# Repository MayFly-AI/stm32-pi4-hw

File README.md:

This repository contains 

- KiCad files for Raspberry Pi HAT Pose sensor
- KiCad files for STM32 Pose sensor
- STL files for camera enclosure
- STL files for enclosure for STM32 Pose sensor

We have used JLCPCB for producing the PCBs and the enclosures.

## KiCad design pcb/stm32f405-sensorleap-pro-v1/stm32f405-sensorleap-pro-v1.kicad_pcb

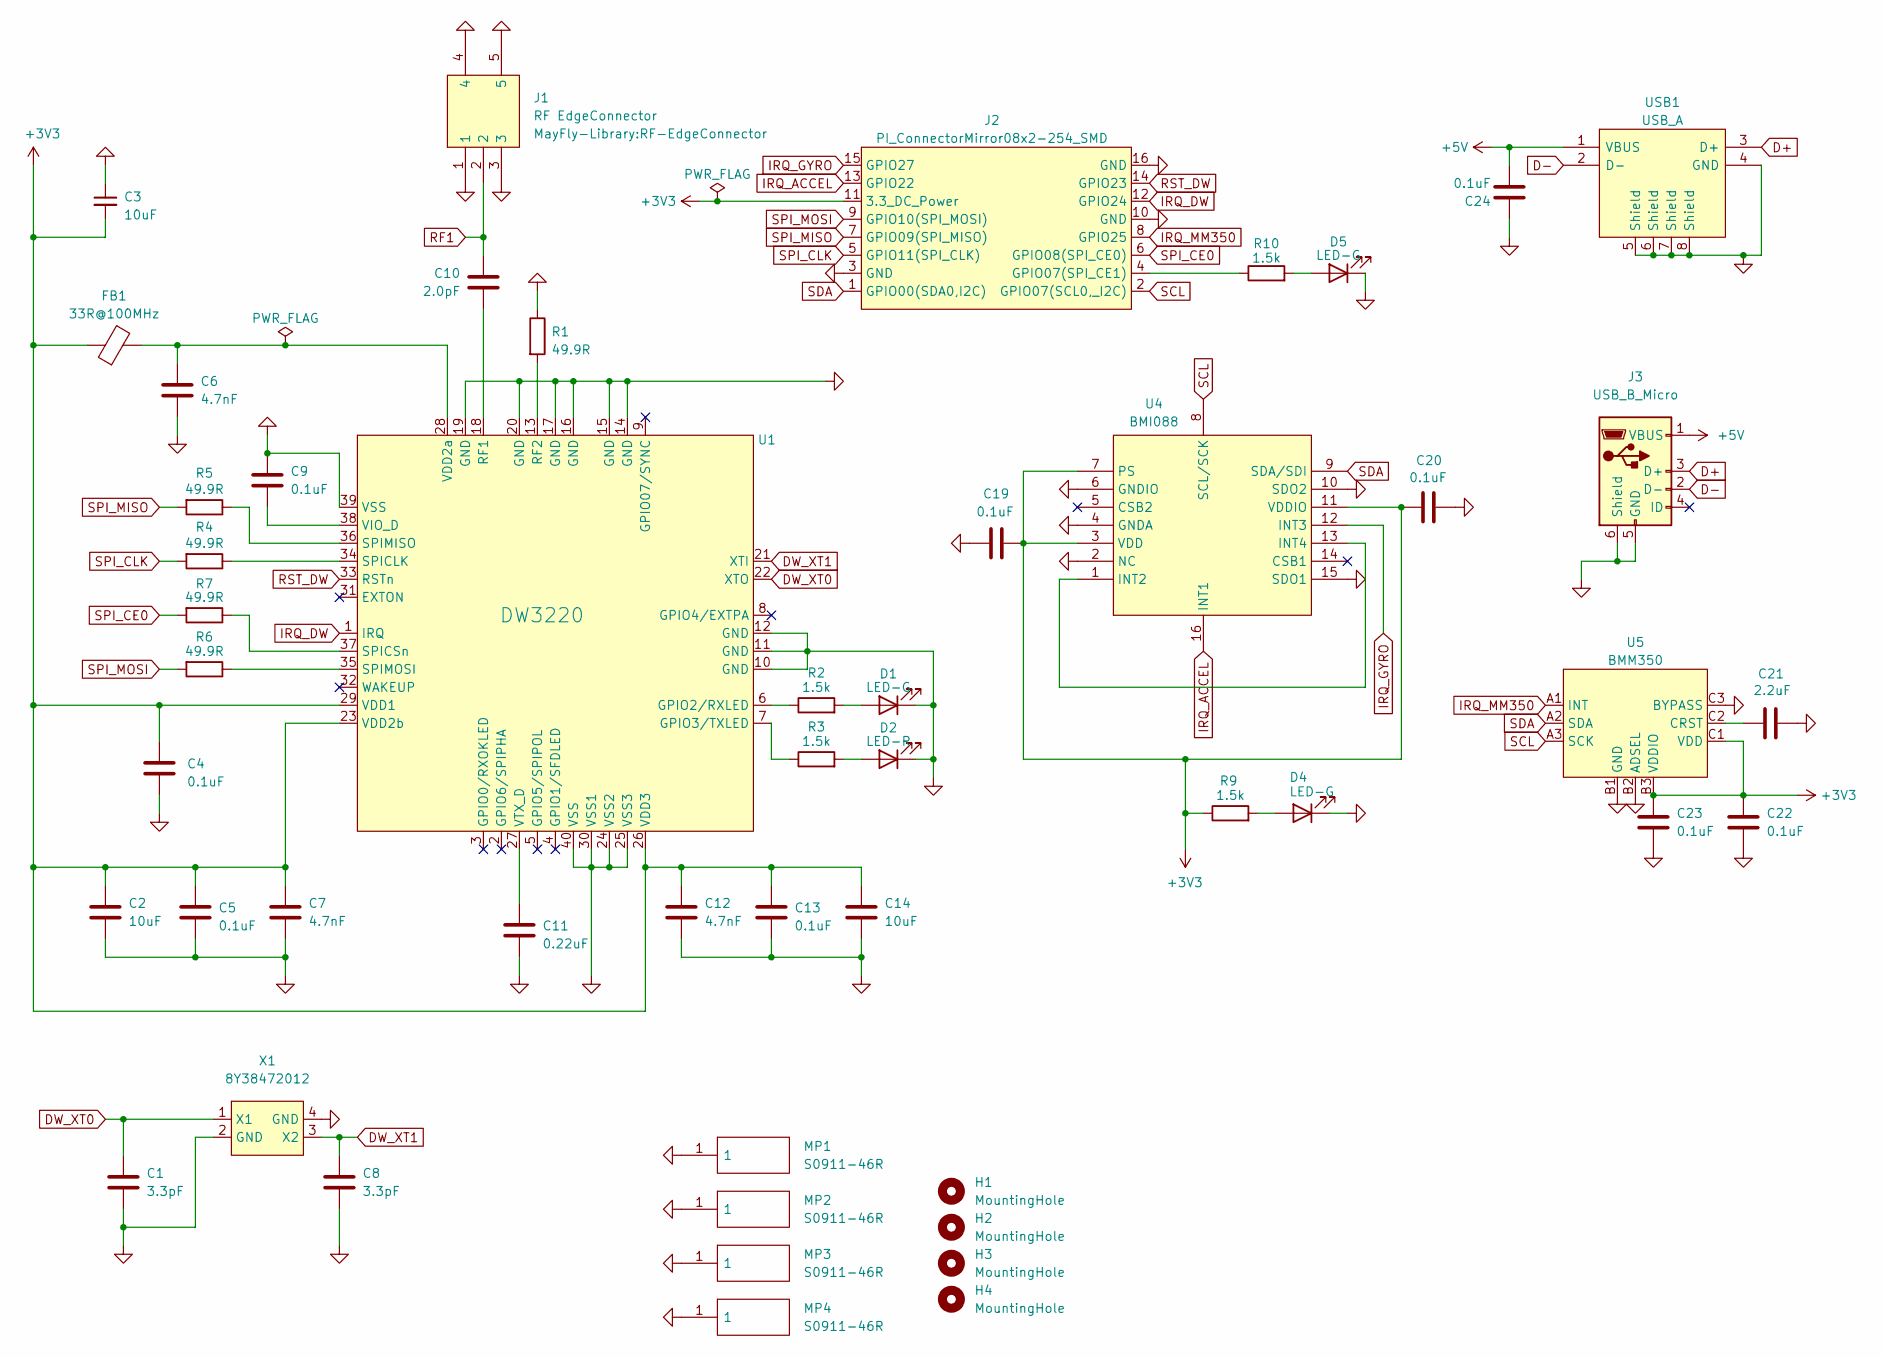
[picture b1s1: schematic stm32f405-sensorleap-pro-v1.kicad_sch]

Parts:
C1, C8: 3.3pF; C_0402_1005Metric; Mouser 81-GJM1555C1H3R3WB1D
C2, C14: 10uF; C_0402_1005Metric; Mouser 81-GRM155R61A106ME1D
C3: 10uF; C_0603_1608Metric; Mouser 81-GRM188R60J106ME47
C4, C5, C9, C13, C19, C20, C22, C23, C24: 0.1uF; C_0402_1005Metric; Mouser 810-C1005X7R1H104KBE
C6, C7, C12: 4.7nF; C_0402_1005Metric; Mouser 81-GCM155R71H472K37D
C10: 2.0pF; C_0402_1005Metric; Mouser 81-GJM1555C1H2R0WB1D
C11: 0.22uF; C_0402_1005Metric; Mouser 81-GRM155R71A224KE1D
C21: 2.2uF; C_0805_2012Metric; Mouser 81-GCM21BR71A225KA7L
D1, D4, D5: LED-G; LED_0603_1608Metric; LCSC C264453
D2: LED-R; LED_0603_1608Metric; LCSC C181863
FB1: 33R@100MHz; L_0402_1005Metric; Mouser 81-BLM15PX330SZ1D
H1, H2, H3, H4: MountingHole; MountingHole_2.5mm
J1: RF EdgeConnector; RF-EdgeConnector
J2: PI_ConnectorMirror08x2-254_SMD; PI_Connector08x2-254_SMD; LCSC C5160823
J3: USB_B_Micro; USB_Micro-AB_Molex_47590-0001; LCSC C136001
MP1, MP2, MP3, MP4: S0911-46R; S091146R; Mouser Part Number 855-S0911-46R
R1, R4, R5, R6, R7: 49.9R; R_0402_1005Metric; Mouser 667-ERJ-2RKF49R9X
R2, R3, R9, R10: 1.5k; R_0402_1005Metric; Mouser 667-ERJ-2RKF1501X
U1: DW3220; QFN-40_5x5_Pitch0.4mm; Mouser 772-DW3220TR13
U4: BMI088; Mouser :262-BMI088
U5: BMM350; LCSC C7496950
USB1: USB_A; 629104190121; Mouser Part Number 710-629104190121
X1: 8Y38472012; LCSC C2450882

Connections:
+3V3: C2.1, C3.2, C4.1, C5.1, C7.1, C12.1, C13.1, C14.1, C19.2, C20.1, C22.1, C23.1, FB1.1, J2.11 (3.3_DC_Power), R9.1, U1.23 (VDD2b), U1.26 (VDD3), U1.29 (VDD1), U4.3 (VDD), U4.7 (PS), U4.11 (VDDIO), U5.B3 (VDDIO), U5.C1 (VDD)
+5V: C24.2, J3.1 (VBUS), USB1.1 (VBUS)
D+: J3.3 (D+), USB1.3 (D+)
D-: J3.2 (D-), USB1.2 (D-)
DW_XT0: C1.1, U1.22 (XTO), X1.1 (X1)
DW_XT1: C8.1, U1.21 (XTI), X1.3 (X2)
GND: C1.2, C2.2, C3.1, C4.2, C5.2, C6.2, C7.2, C8.2, C9.1, C11.2, C12.2, C13.2, C14.2, C19.1, C20.2, C21.2, C22.2, C23.2, C24.1, D1.1 (K), D2.1 (K), D4.1 (K), D5.1 (K), J1.1, J1.3, J1.4, J1.5, J2.3 (GND), J2.10 (GND), J2.16 (GND), J3.5 (GND), J3.6 (Shield), MP1.1, MP2.1, MP3.1, MP4.1, R1.1, U1.10 (GND), U1.11 (GND), U1.12 (GND), U1.14 (GND), U1.15 (GND), U1.16 (GND), U1.17 (GND), U1.19 (GND), U1.20 (GND), U1.24 (VSS2), U1.25 (VSS3), U1.30 (VSS1), U1.39 (VSS), U1.40 (VSS), U4.2 (NC), U4.4 (GNDA), U4.6 (GNDIO), U4.10 (SDO2), U4.15 (SDO1), U5.B1 (GND), U5.B2 (ADSEL), U5.C3 (BYPASS), USB1.4 (GND), USB1.5 (Shield), USB1.6 (Shield), USB1.7 (Shield), USB1.8 (Shield), X1.2 (GND), X1.4 (GND)
IRQ_ACCEL: J2.13 (GPIO22), U4.16 (INT1)
IRQ_DW: J2.12 (GPIO24), U1.1 (IRQ)
IRQ_GYRO: J2.15 (GPIO27), U4.12 (INT3)
IRQ_MM350: J2.8 (GPIO25), U5.A1 (INT)
unnamed: D1.2 (A), R2.2
unnamed: D2.2 (A), R3.2
unnamed: D4.2 (A), R9.2
unnamed: D5.2 (A), R10.2
unnamed: J2.4 (GPIO07(SPI_CE1)), R10.1
unnamed: R2.1, U1.6 (GPIO2/RXLED)
unnamed: R3.1, U1.7 (GPIO3/TXLED)
unnamed: C10.2, U1.18 (RF1)
unnamed: R1.2, U1.13 (RF2)
unnamed: R4.1, U1.34 (SPICLK)
unnamed: R7.1, U1.37 (SPICSn)
unnamed: R5.1, U1.36 (SPIMISO)
unnamed: R6.1, U1.35 (SPIMOSI)
unnamed: C6.1, FB1.2, U1.28 (VDD2a)
unnamed: C9.2, U1.38 (VIO_D)
unnamed: C11.1, U1.27 (VTX_D)
unnamed: U4.1 (INT2), U4.13 (INT4)
unnamed: C21.1, U5.C2 (CRST)
RF1: C10.1, J1.2
RST_DW: J2.14 (GPIO23), U1.33 (RSTn)
SCL: J2.2 (GPIO07(SCL0,_I2C)), U4.8 (SCL/SCK), U5.A3 (SCK)
SDA: J2.1 (GPIO00(SDA0,I2C)), U4.9 (SDA/SDI), U5.A2 (SDA)
SPI_CE0: J2.6 (GPIO08(SPI_CE0)), R7.2
SPI_CLK: J2.5 (GPIO11(SPI_CLK)), R4.2
SPI_MISO: J2.7 (GPIO09(SPI_MISO)), R5.2
SPI_MOSI: J2.9 (GPIO10(SPI_MOSI)), R6.2

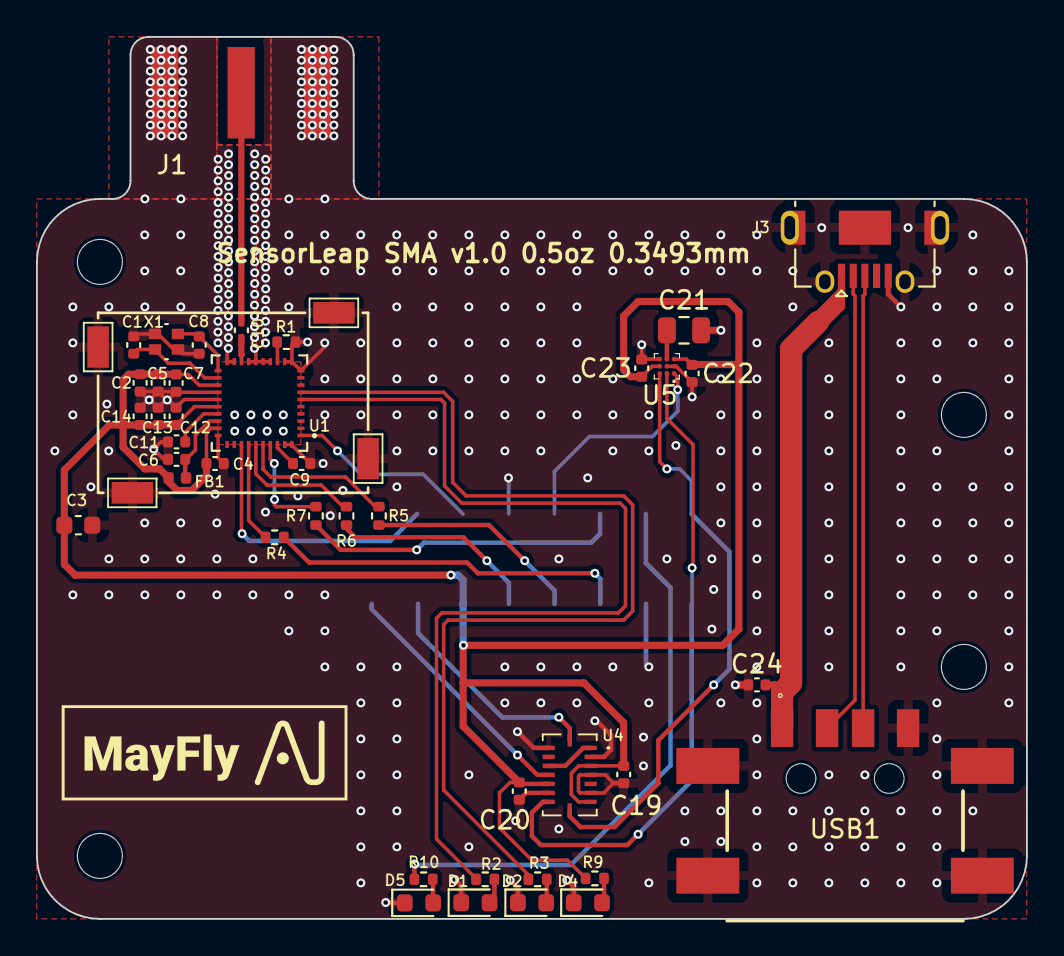
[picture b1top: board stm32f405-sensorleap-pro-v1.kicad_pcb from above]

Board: 4 copper layers, 55.0 x 49.0 mm, 50 parts (1 on the bottom side), 37 nets.

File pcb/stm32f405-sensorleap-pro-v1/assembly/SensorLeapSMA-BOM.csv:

Comment,Designator,Footprint,LCSC
3.3pF,"C1,C8",Capacitor_SMD:C_0402_1005Metric,C88892
2.0pF,C10,Capacitor_SMD:C_0402_1005Metric,C88885
0.22uF,C11,Capacitor_SMD:C_0402_1005Metric,C180472
10uF,"C2,C14",Capacitor_SMD:C_0402_1005Metric,C408132
2.2uF,C21,Capacitor_SMD:C_0805_2012Metric,C126587
10uF,C3,Capacitor_SMD:C_0603_1608Metric,C77041
0.1uF,"C4,C5,C9,C13,C19,C20,C22,C23,C24",Capacitor_SMD:C_0402_1005Metric,C432917
4.7nF,"C6,C7,C12",Capacitor_SMD:C_0402_1005Metric,C85860
LED-G,"D1,D4,D5",LED_SMD:LED_0603_1608Metric,C264453
LED-R,D2,LED_SMD:LED_0603_1608Metric,C181863
33R@100MHz,FB1,Inductor_SMD:L_0402_1005Metric,C2661673
USB_B_Micro,J3,MayFly-Library:USB_Micro-AB_Molex_47590-0001,C136001
49.9R,"R1,R4,R5,R6,R7",Resistor_SMD:R_0402_1005Metric,C441726
1.5k,"R2,R3,R9,R10",Resistor_SMD:R_0402_1005Metric,C413084
DW3220,U1,MayFly-Library:QFN-40_5x5_Pitch0.4mm,C5441013
BMI088,U4,SamacSys_Parts:BMI088,C194919
BMM350,U5,MayFly-Library:BMM350,C7496950
USB_A,USB1,SamacSys_Parts:629104190121,C530629
8Y38472012,X1,MayFly-Library:8Y38472012,C2450882

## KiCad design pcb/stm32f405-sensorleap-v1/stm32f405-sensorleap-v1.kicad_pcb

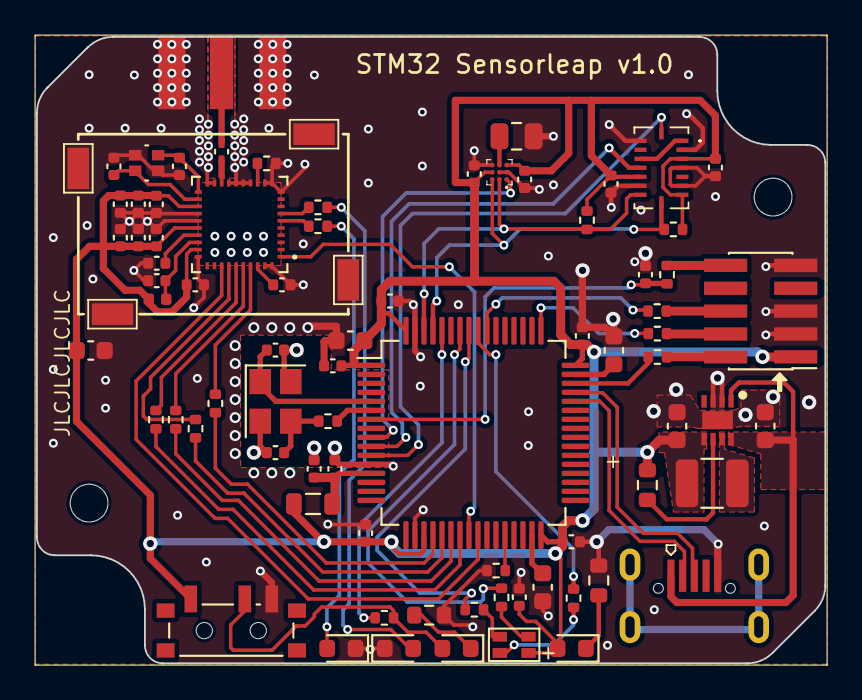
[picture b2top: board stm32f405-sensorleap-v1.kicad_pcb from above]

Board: 4 copper layers, 43.8 x 34.8 mm, 82 parts (0 on the bottom side), 61 nets.

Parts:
C1, C301: 10uF; C_0603_1608Metric
C2, C14: 10uF; C_0402_1005Metric
C3, C9: 3.3pF; C_0402_1005Metric
C4, C6, C7, C13, C15, C16, C18, C19: 0.1uF; C_0402_1005Metric
C5, C8, C12: 4.7nF; C_0402_1005Metric
C10: 2.0pF; C_0402_1005Metric
C11: 0.22uF; C_0402_1005Metric
C20: 2.2uF; C_0805_2012Metric
C200: 4u7; C_0603_1608Metric
C201, C202, C203, C204, C205, C212, C400: 100n; C_0402_1005Metric
C206: 1u; C_0402_1005Metric
C207: 10n; C_0402_1005Metric
C208, C209: 2u2; C_0603_1608Metric
C210, C211: 12p; C_0402_1005Metric
C302: 22uF; C_0603_1608Metric
D1, D102: LED-G; LED_0603_1608Metric
D2, D200: LED-R; LED_0603_1608Metric
D201: 19-237/R6GHBHC-A01/2T; 19-237-R6GHBHC-A01-2T
FB1: 33R@100MHz; L_0402_1005Metric
FB200: 600 @ 600 MHz; L_0805_2012Metric
H1, H2: MountingHole; MountingHole_2.1mm
J1: RF EdgeConnector; CON-SMA-EDGE-SRP
J401: SWD; PinHeader_2x05_P1.27mm_Vertical_SMD
J402: USB_B_Micro; 5P Female Micro-B C40943
L1: 1uH; L_1210_3225Metric
MP1, MP2, MP3, MP4: S0911-46R; S091146R
R1, R2, R3, R4, R5: 49.9R; R_0402_1005Metric
R6, R206, R207, R208: 1k; R_0402_1005Metric
R7: 1.5k; R_0402_1005Metric
R105: 1k5; R_0603_1608Metric
R200: 47R; R_0402_1005Metric
R201, R203: 10k; R_0402_1005Metric
R202: 1k; R_0603_1608Metric
R204, R205: 2k2; R_0402_1005Metric
R301: 180k; R_0603_1608Metric
R400, R401, R402, R403: 22R; R_0402_1005Metric
SW200: SW_SPDT; SW_SPDT_PCM12
U1: DW3220; QFN-40_5x5_Pitch0.4mm
U2: BMI088
U3: BMM350
U200: STM32F405RGT6; LQFP-64_10x10mm_P0.5mm
U301: TPS62082; SON50P200X200X80-9N
X1: 8Y38472012
Y200: 16MHz; Crystal_SMD_3225-4Pin_3.2x2.5mm

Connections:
+3.3VA: C206.1, C207.1, FB200.1, U200.13 (VDDA)
+3V3: C1.2, C2.1, C4.1, C6.1, C8.1, C12.1, C13.1, C14.1, C15.2, C16.1, C18.1, C19.1, C200.1, C201.1, C202.1, C203.1, C204.1, C205.1, C212.1, C302.1, D102.2 (A), D201.4 (A), FB1.1, FB200.2, J401.1, L1.2, R204.1, R205.1, R301.2, SW200.1 (A), U1.23 (VDD2b), U1.26 (VDD3), U1.29 (VDD1), U2.3 (VDD), U2.7 (PS), U2.11 (VDDIO), U3.B3 (VDDIO), U3.C1 (VDD), U200.1 (VBAT), U200.19 (VDD), U200.32 (VDD), U200.48 (VDD), U200.64 (VDD), U301.5 (VOS)
+5V: C301.1, J402.1 (VBUS), U301.1 (EN), U301.8 (VIN)
BOOT0: R201.2, U200.60 (BOOT0)
BOOT1: R203.1, U200.28 (PB2)
DW_XT0: C3.1, U1.22 (XTO), X1.1 (X1)
DW_XT1: C9.1, U1.21 (XTI), X1.3 (X2)
GND: C1.1, C2.2, C3.2, C4.2, C5.2, C6.2, C7.1, C8.2, C9.2, C11.2, C12.2, C13.2, C14.2, C15.1, C16.2, C18.2, C19.2, C20.2, C200.2, C201.2, C202.2, C203.2, C204.2, C205.2, C206.2, C207.2, C208.2, C209.2, C210.2, C211.2, C212.2, C301.2, C302.2, C400.2, D1.1 (K), D2.1 (K), J1.1, J1.3, J1.4, J1.5, J401.3, J401.5, J401.9, J402.5 (GND), MP1.1, MP2.1, MP3.1, MP4.1, R5.1, R105.2, R202.1, R203.2, SW200.3 (C), U1.10 (GND), U1.11 (GND), U1.12 (GND), U1.14 (GND), U1.15 (GND), U1.16 (GND), U1.17 (GND), U1.19 (GND), U1.20 (GND), U1.24 (VSS2), U1.25 (VSS3), U1.30 (VSS1), U1.39 (VSS), U1.40 (VSS), U2.2 (NC), U2.4 (GNDA), U2.6 (GNDIO), U2.10 (SDO2), U2.15 (SDO1), U3.B1 (GND), U3.B2 (ADSEL), U3.C3 (BYPASS), U200.12 (VSSA), U200.18 (VSS), U200.63 (VSS), U301.2 (GND), U301.3 (MODE), U301.9 (GND), X1.2 (GND), X1.4 (GND), Y200.2, Y200.4
HSE_IN: C210.1, U200.5 (PH0), Y200.1
HSE_OUT: R200.1, U200.6 (PH1)
I2C1_SCL: R204.2, U2.8 (SCL/SCK), U3.A3 (SCK), U200.61 (PB8)
I2C1_SDA: R205.2, U2.9 (SDA/SDI), U3.A2 (SDA), U200.62 (PB9)
INT_ACC: U2.16 (INT1), U200.11 (PC3)
INT_GYR: U2.12 (INT3), U200.10 (PC2)
IRQ_DW: U1.1 (IRQ), U200.24 (PC4)
IRQ_MM350: U3.A1 (INT), U200.9 (PC1)
NRST: C400.1, R403.1, U200.7 (NRST)
unnamed: C211.1, R200.2, Y200.3
unnamed: D1.2 (A), R6.2
unnamed: D2.2 (A), R7.2
unnamed: D102.1 (K), R105.1
unnamed: D200.2 (A), R201.1, SW200.2 (B)
unnamed: D200.1 (K), R202.2
unnamed: D201.3 (BK), R208.1
unnamed: D201.2 (GK), R207.1
unnamed: D201.1 (RK), R206.1
unnamed: J401.2, R400.2
unnamed: J401.4, R401.2
unnamed: J401.6, R402.2
unnamed: J401.10, R403.2
unnamed: R6.1, U1.6 (GPIO2/RXLED)
unnamed: R7.1, U1.7 (GPIO3/TXLED)
unnamed: C10.2, U1.18 (RF1)
unnamed: R5.2, U1.13 (RF2)
unnamed: R2.1, U1.34 (SPICLK)
unnamed: R3.1, U1.37 (SPICSn)
unnamed: R1.1, U1.36 (SPIMISO)
unnamed: R4.1, U1.35 (SPIMOSI)
unnamed: C5.1, FB1.2, U1.28 (VDD2a)
unnamed: C7.2, U1.38 (VIO_D)
unnamed: C11.1, U1.27 (VTX_D)
unnamed: U2.1 (INT2), U2.13 (INT4)
unnamed: C20.1, U3.C2 (CRST)
unnamed: C208.1, U200.31 (VCAP_1)
unnamed: C209.1, U200.47 (VCAP_2)
unnamed: R301.1, U301.6 (PG)
unnamed: L1.1, U301.7 (SW)
RF1: C10.1, J1.2
RST_DW: U1.33 (RSTn), U200.25 (PC5)
SPI1_!CS_ACC: R3.2, U200.20 (PA4)
SPI1_MISO: R1.2, U200.22 (PA6)
SPI1_MOSI: R4.2, U200.23 (PA7)
SPI1_SCK: R2.2, U200.21 (PA5)
SWCLK: R401.1, U200.49 (PA14)
SWDIO: R400.1, U200.46 (PA13)
SWO: R402.1, U200.55 (PB3)
TIM3_CH1: R206.2, U200.56 (PB4)
TIM3_CH2: R207.2, U200.57 (PB5)
TIM4_CH1: R208.2, U200.58 (PB6)
USB_D+: J402.3 (D+), U200.45 (PA12)
USB_D-: J402.2 (D-), U200.44 (PA11)

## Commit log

2024-02-19 add files
2024-02-20 pro version
2024-02-29 adjust pi4 box to fit pro board
2024-03-07 pi4 geometry files and gitignore kicad cache and backup
